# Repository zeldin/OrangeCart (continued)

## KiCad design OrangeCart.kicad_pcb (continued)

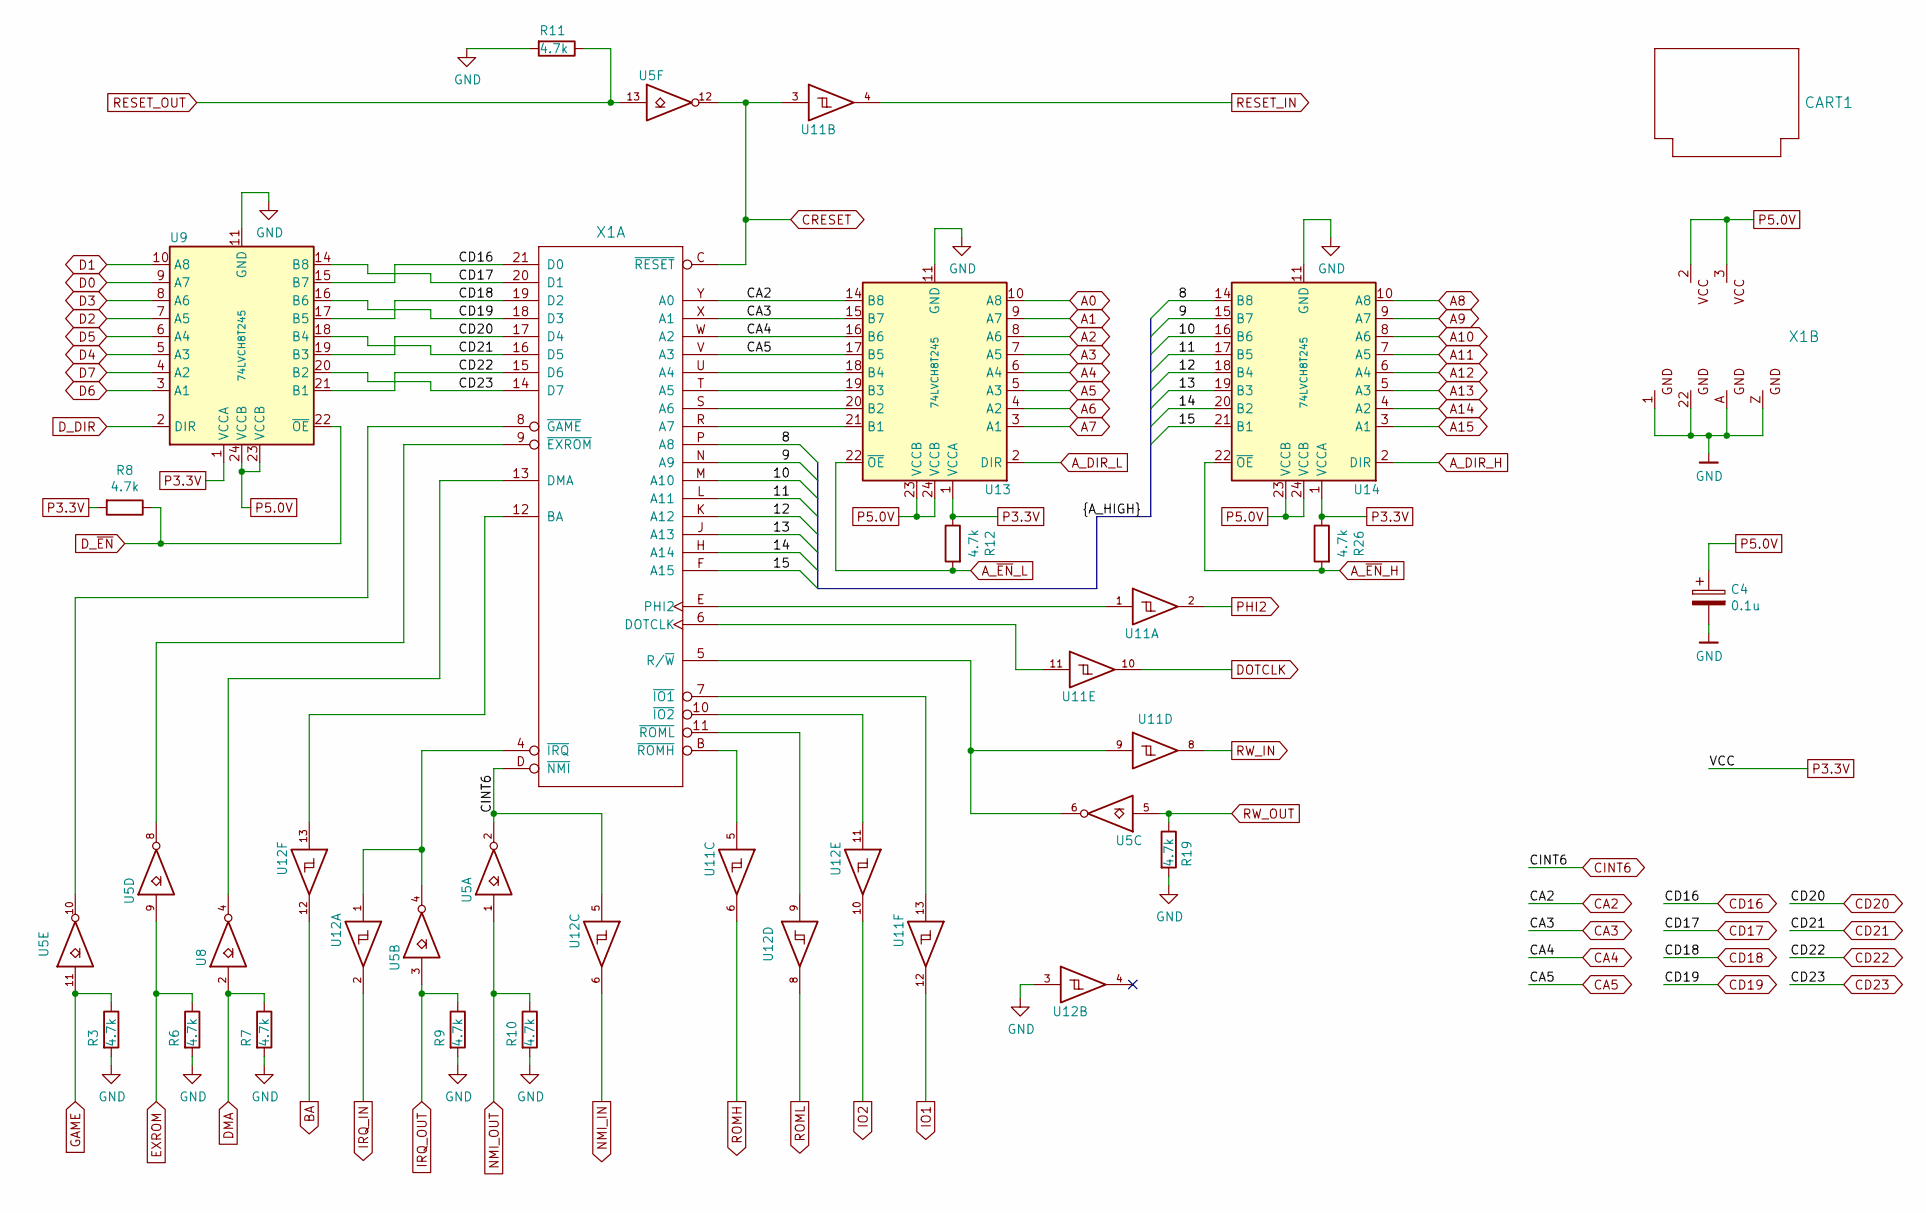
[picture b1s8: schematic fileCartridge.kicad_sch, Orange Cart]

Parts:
C4: 0.1u; C_0603_1608Metric; Mouser Part No 710-885012206071
CART1: CARTRIDGE_C64; CARTRIDGE_C64_GERMAN
R3, R6, R7, R8, R9, R10, R11, R12, R19, R26: 4.7k; R_0402_1005Metric; Mouser Part No 603-RC0402JR-074K7L
U5: 74LVC06A; TSSOP-14_4.4x5mm_P0.65mm; Mouser Part No 595-SN74LVC06APW
U8: 74LVC1G06; SOT-23-5; Mouser Part No 595-SN74LVC1G06DBVR
U9, U13, U14: 74LVCH8T245; TSSOP-24_4.4x7.8mm_P0.65mm; Mouser Part No 771-4LVCH8T245PWQ10J
U11, U12: 74AHCV17A; TSSOP-14_4.4x5mm_P0.65mm; Mouser Part No 771-74AHCV17APWJ
X1: EXPANSION_PORT_C64_EDGE; MA100-22-2

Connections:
/sheetCartridge/8: U14.14 (B8), X1.P (A8)
/sheetCartridge/9: U14.15 (B7), X1.N (A9)
/sheetCartridge/10: U14.16 (B6), X1.M (A10)
/sheetCartridge/11: U14.17 (B5), X1.L (A11)
/sheetCartridge/12: U14.18 (B4), X1.K (A12)
/sheetCartridge/13: U14.19 (B3), X1.J (A13)
/sheetCartridge/14: U14.20 (B2), X1.H (A14)
/sheetCartridge/15: U14.21 (B1), X1.F (A15)
A0: U13.10 (A8); also elsewhere on the board
A1: U13.9 (A7); also elsewhere on the board
A2: U13.8 (A6); also elsewhere on the board
A3: U13.7 (A5); also elsewhere on the board
A4: U13.6 (A4); also elsewhere on the board
A5: U13.5 (A3); also elsewhere on the board
A6: U13.4 (A2); also elsewhere on the board
A7: U13.3 (A1); also elsewhere on the board
A8: U14.10 (A8); also elsewhere on the board
A9: U14.9 (A7); also elsewhere on the board
A10: U14.8 (A6); also elsewhere on the board
A11: U14.7 (A5); also elsewhere on the board
A12: U14.6 (A4); also elsewhere on the board
A13: U14.5 (A3); also elsewhere on the board
A14: U14.4 (A2); also elsewhere on the board
A15: U14.3 (A1); also elsewhere on the board
A_DIR_H: U14.2 (DIR); also elsewhere on the board
A_DIR_L: U13.2 (DIR); also elsewhere on the board
A_~EN_H: R26.2, U14.22 (~OE); also elsewhere on the board
A_~EN_L: R12.2, U13.22 (~OE); also elsewhere on the board
BA: U12.12; also elsewhere on the board
CA2: U13.14 (B8), X1.Y (A0); also elsewhere on the board
CA3: U13.15 (B7), X1.X (A1); also elsewhere on the board
CA4: U13.16 (B6), X1.W (A2); also elsewhere on the board
CA5: U13.17 (B5), X1.V (A3); also elsewhere on the board
CD16: U9.15 (B7), X1.21 (D0); also elsewhere on the board
CD17: U9.14 (B8), X1.20 (D1); also elsewhere on the board
CD18: U9.17 (B5), X1.19 (D2); also elsewhere on the board
CD19: U9.16 (B6), X1.18 (D3); also elsewhere on the board
CD20: U9.19 (B3), X1.17 (D4); also elsewhere on the board
CD21: U9.18 (B4), X1.16 (D5); also elsewhere on the board
CD22: U9.21 (B1), X1.15 (D6); also elsewhere on the board
CD23: U9.20 (B2), X1.14 (D7); also elsewhere on the board
CINT6: U5.2, U12.5, X1.D (~NMI); also elsewhere on the board
CRESET: U5.12, U11.3, X1.C (~RESET); also elsewhere on the board
D0: U9.9 (A7); also elsewhere on the board
D1: U9.10 (A8); also elsewhere on the board
D2: U9.7 (A5); also elsewhere on the board
D3: U9.8 (A6); also elsewhere on the board
D4: U9.5 (A3); also elsewhere on the board
D5: U9.6 (A4); also elsewhere on the board
D6: U9.3 (A1); also elsewhere on the board
D7: U9.4 (A2); also elsewhere on the board
DMA: R7.1, U8.2; also elsewhere on the board
DOTCLK: U11.10; also elsewhere on the board
D_DIR: U9.2 (DIR); also elsewhere on the board
D_~EN: R8.1, U9.22 (~OE); also elsewhere on the board
EXROM: R6.1, U5.9; also elsewhere on the board
GAME: R3.1, U5.11; also elsewhere on the board
GND: C4.2, R3.2, R6.2, R7.2, R9.2, R10.2, R11.2, R19.2, U5.7 (GND), U8.3 (GND), U9.11 (GND), U9.12 (GND), U9.13 (GND), U11.7 (GND), U12.3, U12.7 (GND), U13.11 (GND), U13.12 (GND), U13.13 (GND), U14.11 (GND), U14.12 (GND), U14.13 (GND), X1.1 (GND), X1.22 (GND@1), X1.A (GND@2), X1.Z (GND@3); also elsewhere on the board
IO1: U11.12; also elsewhere on the board
IO2: U12.10; also elsewhere on the board
IRQ_IN: U12.2; also elsewhere on the board
IRQ_OUT: R9.1, U5.3; also elsewhere on the board
NMI_IN: U12.6; also elsewhere on the board
NMI_OUT: R10.1, U5.1; also elsewhere on the board
unnamed: U13.21 (B1), X1.R (A7)
unnamed: U13.20 (B2), X1.S (A6)
unnamed: U13.19 (B3), X1.T (A5)
unnamed: U13.18 (B4), X1.U (A4)
unnamed: U12.13, X1.12 (BA)
unnamed: U8.4, X1.13 (DMA)
unnamed: U11.11, X1.6 (DOTCLK)
unnamed: U11.1, X1.E (PHI2)
unnamed: U5.6, U11.9, X1.5 (R/~W)
unnamed: U5.8, X1.9 (~EXROM)
unnamed: U5.10, X1.8 (~GAME)
unnamed: U11.13, X1.7 (~IO1)
unnamed: U12.11, X1.10 (~IO2)
unnamed: U5.4, U12.1, X1.4 (~IRQ)
unnamed: U11.5, X1.B (~ROMH)
unnamed: U12.9, X1.11 (~ROML)
P3.3V: R8.2, R12.1, R26.1, U5.14 (VCC), U8.5 (VCC), U9.1 (VCCA), U11.14 (VCC), U12.14 (VCC), U13.1 (VCCA), U14.1 (VCCA); also elsewhere on the board
P5.0V: C4.1, U9.23 (VCCB), U9.24 (VCCB), U13.23 (VCCB), U13.24 (VCCB), U14.23 (VCCB), U14.24 (VCCB), X1.2 (VCC), X1.3 (VCC@1); also elsewhere on the board
PHI2: U11.2; also elsewhere on the board
RESET_IN: U11.4; also elsewhere on the board
RESET_OUT: R11.1, U5.13; also elsewhere on the board
ROMH: U11.6; also elsewhere on the board
ROML: U12.8; also elsewhere on the board
RW_IN: U11.8; also elsewhere on the board
RW_OUT: R19.1, U5.5; also elsewhere on the board

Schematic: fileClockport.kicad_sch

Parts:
J1: Conn_02x11_Odd_Even; PinHeader_2x11_P2.00mm_Vertical; Mouser Part No 200-TMM11103GD
RN1: 10K; R_Array_Convex_4x0402; Mouser Part No 667-EXB-28V103JX

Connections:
CA2: J1.12; also elsewhere on the board
CA3: J1.11; also elsewhere on the board
CA4: J1.10; also elsewhere on the board
CA5: J1.9; also elsewhere on the board
CD16: J1.20; also elsewhere on the board
CD17: J1.19; also elsewhere on the board
CD18: J1.18; also elsewhere on the board
CD19: J1.17; also elsewhere on the board
CD20: J1.16; also elsewhere on the board
CD21: J1.15; also elsewhere on the board
CD22: J1.14; also elsewhere on the board
CD23: J1.13; also elsewhere on the board
CINT6: J1.3; also elsewhere on the board
CIORD: J1.7, RN1.2 (R2.1); also elsewhere on the board
CIOWR: J1.8, RN1.1 (R1.1); also elsewhere on the board
CRESET: J1.22; also elsewhere on the board
CRTCCS: J1.5, RN1.3 (R3.1); also elsewhere on the board
CSPARECS: J1.4, RN1.4 (R4.1); also elsewhere on the board
GND: J1.1, J1.21; also elsewhere on the board
P3.3V: RN1.5 (R4.2), RN1.6 (R3.2), RN1.7 (R2.2), RN1.8 (R1.2); also elsewhere on the board
P5.0V: J1.2; also elsewhere on the board

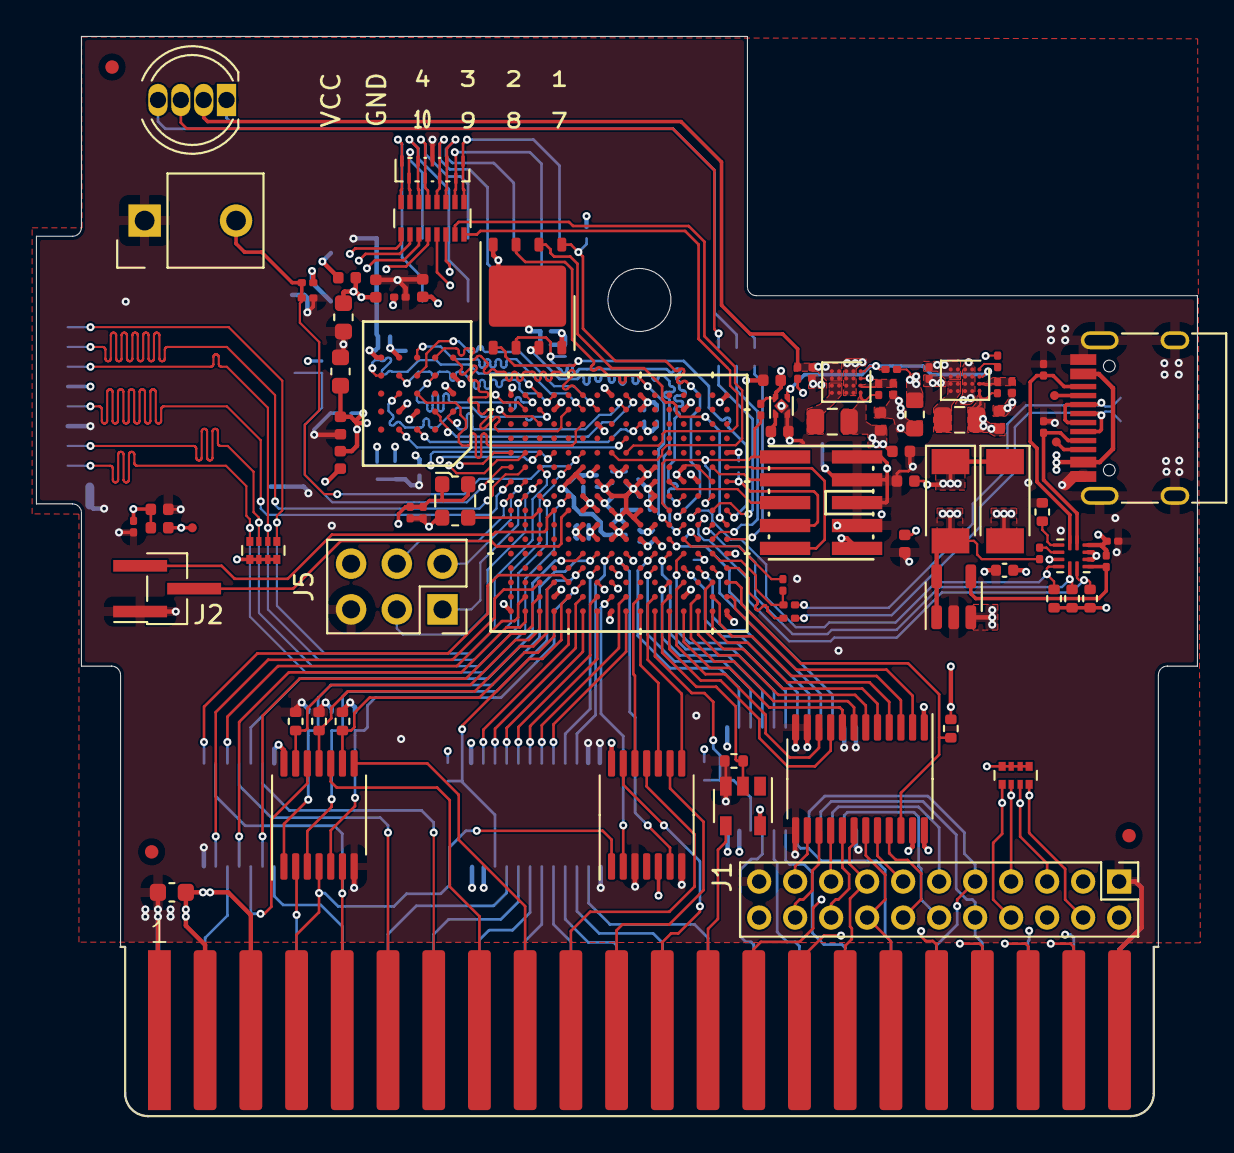
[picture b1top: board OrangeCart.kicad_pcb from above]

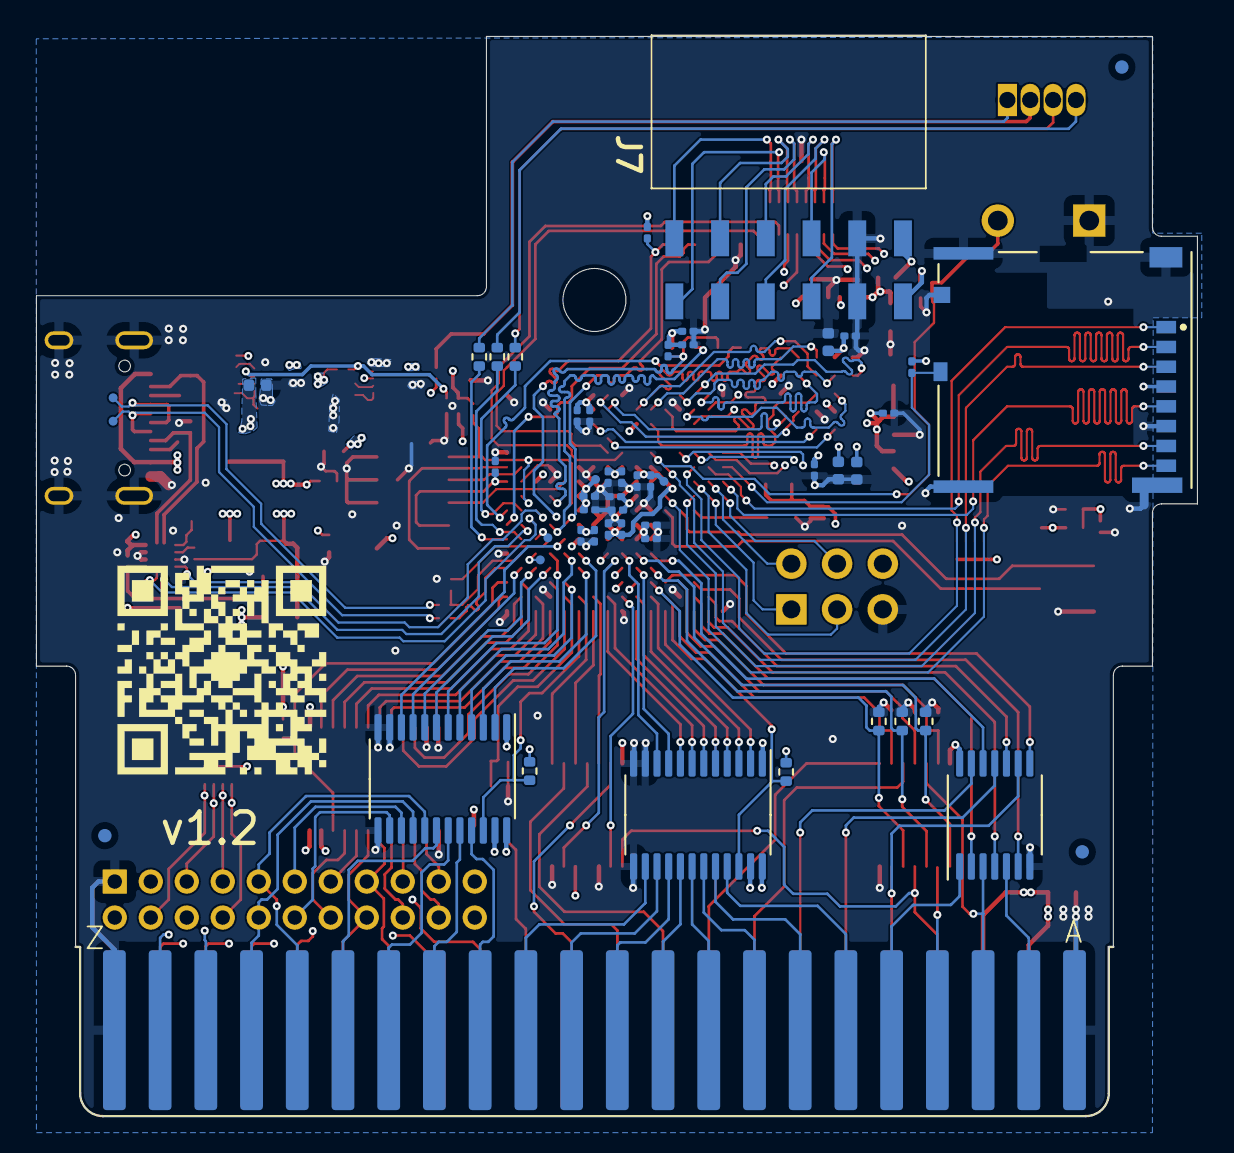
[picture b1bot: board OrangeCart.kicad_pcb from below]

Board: 4 copper layers, 64.5 x 60.0 mm, 140 parts (52 on the bottom side), 185 nets.

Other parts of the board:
QR1: qr

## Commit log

2021-02-28 Add 3d model for diodes
2021-03-14 Add clockport
2021-03-14 Add pullups of clockport signals
2021-03-14 Retune RAM_PSC
2021-03-14 Fix bank 6 voltage indication in schematic
2021-03-14 Keep out copper pour from card edge connector, and hide references
2021-03-14 Move stuff around in preparation for USB mini-B connector
2021-03-14 Replace USB micro-B connector with mini-B
2021-03-28 Update BOM with Mouser sourcing information
2021-03-30 Length match SPI flash and SDCARD signals
2021-03-30 Add QR code
2021-04-12 Remove solder paste on card edge connector
2021-05-19 Increase via annular, and decrease min clearance
2021-05-19 Replace schematic symbol of FPGA with 0.8mm pitch version
2021-05-19 Replace footprint of FPGA with 0.8mm pitch version
2021-05-20 Mark I/O banks
2021-05-20 Swap bank 2 and 6
2021-05-20 Increase via size
2021-05-22 Fix remaining DRC violations after dimension changes
2021-05-22 Move USB tracks
2021-05-22 Reconnect JTAG
2021-05-22 Reconnect QSPI and LED
2021-05-22 Reconnect RAM
2021-05-23 Reconnect SDCARD and add a serial port
2021-05-23 Move tracks from inner layer 2 to 3
2021-05-23 Reconnect expansion port
2021-05-23 Disable I/O bank 0 and 3
2021-05-23 Restore power and decouplings
2021-05-23 Update BOM
2021-05-23 Connect some unconnected stuff
2021-05-23 Length match SDCARD
2021-05-23 Reduce layers to 4
2021-05-23 Hook up last two GND pins
2021-05-24 Retune track lengths
2021-05-27 Rotate UART connector
2021-06-04 Fix BOM for pin header J1
2021-06-04 Update fab layers
2021-09-04 BOM update: Lower profile headers for J1 and J6
2021-09-04 Replace LED with THT version
2021-09-04 Replace pushbutton with THT version
2021-09-04 Moved fiducials
2021-09-04 Add copper pour to front layer
2021-09-04 Move UART connector
2021-09-17 Adjust RGB LED resistors after measurements
    Measurement over resistors in testbench gave
    R: 2.52V -> 210 ohm for 12.0 mA
    G: 1.5V -> 124 ohm for 12.1 mA
    B: 1.48V -> 124 ohm for 11.9 mA
2021-10-05 Add some more margin between traces and board edge
2021-10-16 Adjust screw hole position
2021-10-17 Change SDcard part
2021-11-20 BOM update: Replace OSC1 with more readily available part
2021-12-04 Update 3D models for pin headers
2021-12-05 Change oscillator from 25 ppm to 50 ppm part (25 ppm was a mistake)
2022-01-14 Replace USB connector with type C
2022-01-23 Add 4 GPIOs on a sort of "Pmod" connector
2022-01-25 Move USB connector 0.05 mm right to provide 1.85 mm clearance to plug
2022-01-26 Change USB-C connector to variant with longer stakes
2022-02-06 Update measurements
2022-02-11 Align BOM with P1 order
2022-02-12 Add CERN OHL licence
2022-02-12 Use new 3D model for USB-C connector
2022-02-14 Update OSC1 footprint
2022-03-06 Add a basic README
2022-04-09 Add weak pull-up resistor to FPGA_RESET
2022-04-30 Change HyperRAM to one with less excessive temperature range
2022-04-30 Add version number on silkscreen
2022-09-25 Add wiki link to README
2022-09-25 Convert to KiCAD 6
2022-09-25 Fix solder mask color
2022-09-25 Fix some checker complaints
2022-09-25 Update Mouser prices
2022-09-25 Replace HyperRAM with 3V Winbond part
    Also remove PSC/PSC# as they are not used on 3V parts.
2022-09-25 Remove 1.8V power supply
2022-09-25 Make traces on inner layers thicker
2022-09-25 Redo routing to memories
2022-09-25 Add NMI and IRQ inputs
2022-09-25 Update datasheet link for HyperRAM
2022-09-25 Add a dual PMOD connector with official shape
2022-09-25 Adjust paste on U10 so that it doesn't extend outside mask
2022-09-25 Fix U12 silkscreen and fab
2022-09-25 Replace 8-channel level shifters with LVCH variant
    The "H" makes them consume less current when the inputs are floating.
2022-09-25 Add USB-C power management chip
2022-09-25 Update version on silk screen
2023-07-31 Convert to KiCAD 7
2023-07-31 Add silkscreen pinout for PMOD
2023-08-01 ERC/DRC updates
2023-08-01 Update net names to match schematic
2023-08-01 Update component prices
2023-08-02 Some plotting setting updates
2023-08-04 Increased size of flash thermal pad
